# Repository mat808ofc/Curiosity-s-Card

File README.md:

# Curiosity's Card

### About
This is a custom business card with a nfc chip "NT3H2111W0FHKH", antenna "NXP's official Class 4 antenna" and a low-current 0603 package red LED, Vishay's "TLMS1000-GS15", which at 2mA (it's tested current for usage) only needs 1.75V (according to the Vf vs. If graphic in the datasheet). This is because the LED will work with the chip's energy harvesting feature, which will "harvest" energy from the nfc device (like a phone). The total voltage the chip can usually output with this technique is 2V, so the LED is inside the budget. I used the Ohm's Law to find the resistor value for the LED. 

R = (V_supply - V_LED) / I_desired

Vf - The forward voltage is the voltage it needs for a given current.
If - The forward current is the current actually flowing through the LED. Controls brightness. This is the value you target. Everything else in the calculation exists to make sure this number ends up where you want it.
They are related to each other. When more current flows through, Vf goes up as well.
V_supply: the total voltage available from the source (VOUT, ~2V in this case)
V_LED (Vf): the voltage the LED itself consumes at THE CHOSEN CURRENT!!

R = (2 − 1.75) / 0.002A = 125Ω, which is approx. 130Ω.

Aside from calculations, I also added personal branding, the Hack Club logo, some cool gradients, a qr code to my github repos and a section with most of the SMD package sizes (It's fun).

### INSPIRATION:
I haven't done projects for quite a long time because I was exhausted from it since the Flight controller (I was also working on my RC plane) so I decided to make a little weekend project, a custom business card, which is also I have honestly been wanting to make for quite a while now.

### CHALLENGES:
My biggest challenge was understanding the math and physics for the LED, it seemed super confusing at first but now I get it, and it makes a lot of sense. I also found it hard to understand the nfc chip and tag, but I ended up figuring it out.

### BOM:
| Part                              | MFR.Part #                  | Qty        | Total Cost (USD) |  Link to part (lcsc)                                                                | Distributor |
|-----------------------------------|-----------------------------|------------|------------------|-------------------------------------------------------------------------------------|-------------|
| C1 (200nf 0603 capacitor)         |  0603B204K160CT             |  20        |    $0.9140       |    https://www.lcsc.com/pt/product-detail/C3833176.html?s_z=n_q_0603B204K160CT      | JLCPCB      |
| D1 (TLMS1000 0603 LED)            |  TLMS1000-GS15              |  5         |    $0.8605       |    https://www.lcsc.com/pt/product-detail/C23070302.html?s_z=n_q_TLMS1000-GS15      | JLCPCB      |
| R1 (130Ω 0402 resistor)           |  RC0402FR-07130RL           |  20        |    $0.0800       |    https://www.lcsc.com/pt/product-detail/C477610.html?s_z=n_q_RC0402FR-07130RL     | JLCPCB      |
| U1 (NXP NT3H2111W0FHKH)           |  NT3H2111W0FHKH             |  2         |    $1.2324       |    https://www.lcsc.com/pt/product-detail/C710403.html?s_z=n_q_NT3H2111W0FHKH       | JLCPCB      |
| Total: $3,0869                    |

JLCPCB quote for assembly of 2 boards + shipping (Global Standard Direct Line: $8.48) + components with -$10 coupon: $26.76

(You can find the excel full BOM file in the project files)

# Grand Total: $26.76

### Extras:

This project does not need a case or anything 3D printed or designed, it is just a business card.
If you have any questions, DM me on slack: Mateus (mateus.flecha808)

## Schematic

## PCB

## Render

The resistors on the SMD package sizing sections WILL NOT be assembled on the pcb! It will just be the footprints to display the different sizes.

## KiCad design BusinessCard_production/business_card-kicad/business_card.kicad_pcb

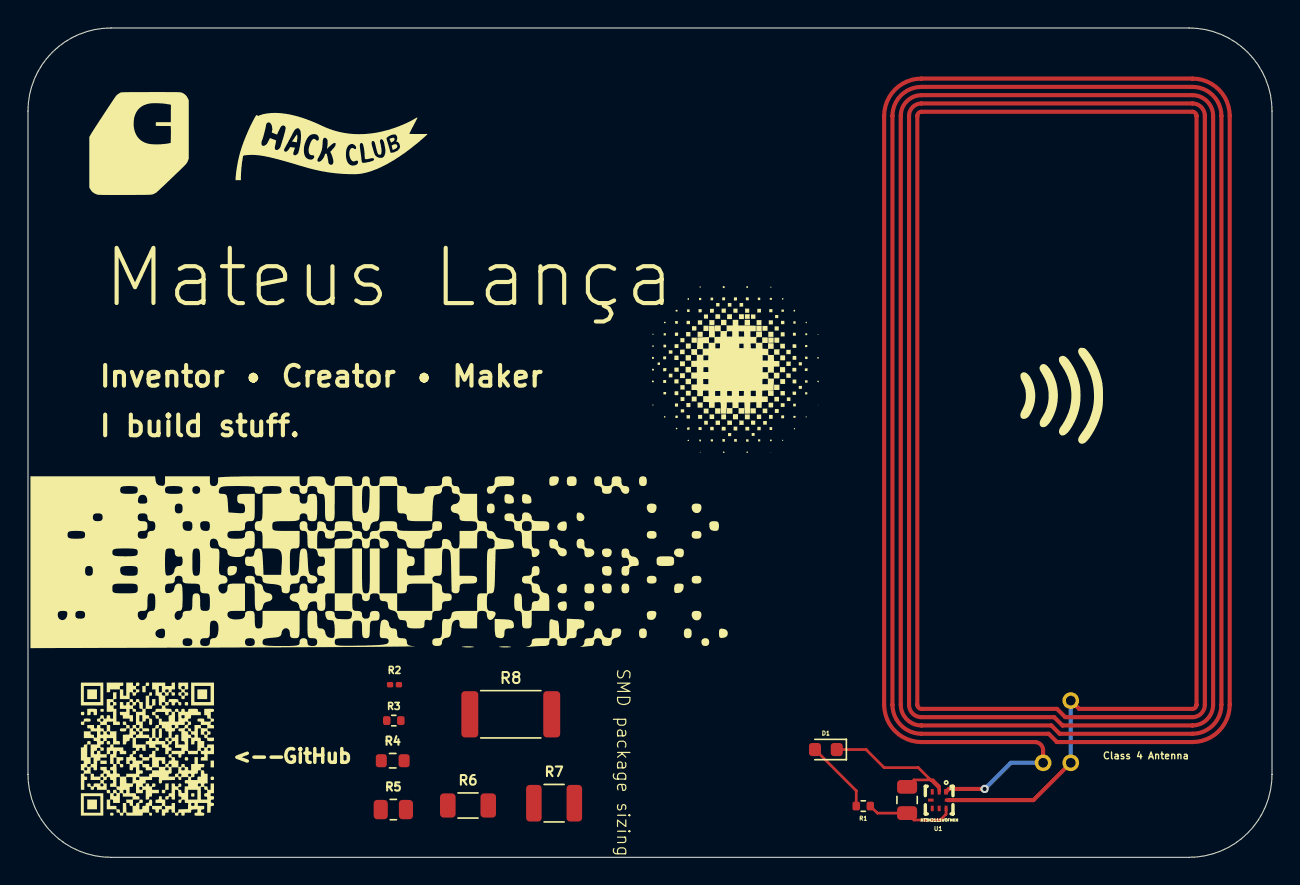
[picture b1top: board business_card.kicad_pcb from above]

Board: 2 copper layers, 90.0 x 60.0 mm, 12 parts (0 on the bottom side), 4 nets.

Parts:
C1: 200nF; C_0805_2012Metric
D1: TLMS1000; LED_0603_1608Metric
E$1: L_PICC_CLASS4_50PF_01
R1: 130; R_0402_1005Metric
R2: R; R_0201_0603Metric
R3: R; R_0402_1005Metric
R4: R; R_0603_1608Metric
R5: R; R_0805_2012Metric
R6: R; R_1206_3216Metric
R7: R; R_1210_3225Metric
R8: R; R_2512_6332Metric
U1: NT3H2111W0FHKH; XQFN-8_L1.6-W1.6-P0.50-BL_NT3H2111W0FHKH

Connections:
/ANTENNA_LB: E$1.P$1, U1.8 (LB)
unnamed: D1.2 (A), R1.1
unnamed: C1.1, D1.1 (K), U1.2 (VSS)
unnamed: C1.2, R1.2, U1.7 (VOUT)

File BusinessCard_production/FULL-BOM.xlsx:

Components BOM
Part | MFR.Part # | Qty | Unit Cost (USD) | Total Cost (USD) | Link to part (LCSC) | Distributor
C1 (200nF 0603 capacitor) | 0603B204K160CT | 20 | 4.5700000000000005E-2 | 0.91400000000000003 | https://www.lcsc.com/pt/product-detail/C3833176.html?s_z=n_q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 | JLCPCB
D1 (TLMS1000 0603 LED) | TLMS1000-GS15 | 5 | 0.1721 | 0.86050000000000004 | https://www.lcsc.com/pt/product-detail/C23070302.html?s_z=n_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 | JLCPCB
R1 (130Ω 0402 resistor) | RC0402FR-07130RL | 20 | 4.0000000000000001E-3 | 0.08 | https://www.lcsc.com/pt/product-detail/C477610.html?s_z=n_q_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 | JLCPCB
U1 (NXP NT3H2111W0FHKH) | NT3H2111W0FHKH | 2 | 0.61619999999999997 | 1.2323999999999999 | https://www.lcsc.com/pt/product-detail/C710403.html?s_z=n_q_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 | JLCPCB
 |  |  | Components Total: | 3.0869
Note: Part qty is the minimum order qty from lcsc
JLCPCB Fabrication & Assembly Quote
Item | Details | Qty | Build Time | Price (USD)
PCB Prototype (business_card_Y10) | Y10-11917019A, Black, 1.2mm Thickness, HASL (with lead) — Special offer price (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 | 5 | 24 hours | 2
PCBA — Economic Assembly (top side) | SMT026100460931-11..., business_card_Y10 | 2 | 1-2 days | 26.28
 |  |  | Merchandise Total: | 28.28
 |  |  | Shipping Estimated (Global Standard Direct Line): | 8.48
 |  |  | Coupon: | -10
 |  |  | Subtotal (Order Total): | 26.760000000000005
Grand Total (JLCPCB Order)
 |  |  | JLCPCB Order Subtotal: | 26.760000000000005
 |  |  | GRAND TOTAL: | 26.760000000000005
